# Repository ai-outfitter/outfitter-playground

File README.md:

# Playground

> [!IMPORTANT]
> This review branch is the PCB-workflow playground. It temporarily pins the
> stacked community-profiles work in PRs
> [#88](https://github.com/ai-outfitter/community-profiles/pull/88),
> [#90](https://github.com/ai-outfitter/community-profiles/pull/90), and
> [#96](https://github.com/ai-outfitter/community-profiles/pull/96), and
> [#102](https://github.com/ai-outfitter/community-profiles/pull/102), selects
> `hardware-engineer`, and enables `pcb-design`. The profile is exercised
> against `hardware/pnb-1`: an ESP32-S3 board whose shared I2C bus carries an
> SCD41 CO2 sensor and BH1750 light sensor. Run `npm run pcb:build` to rebuild
> the routed board and its JLCPCB-compatible fabrication package.
>
> `npm run test:pcb-workflow` still checks the workflow's consumer resolution
> independently. `npm run pcb:build` proves the design toolchain, including a
> live KiCad MCP inventory/project/schematic-ERC/board validation, typed ERC
> with injected failures, numerical margins, pcbnew construction, a validated
> routed seed (with explicit bounded freerouting regeneration), all-severity DRC, and
> Gerber/BOM/CPL generation. Its supplier gate must match every fitted part and
> record PCB, component, assembly, shipping, tariff/duty, tax, and other fees
> as one reconciled landed-cost quote. It never submits an order and cannot
> establish physical acceptance. Replace the branch pin with the release
> containing the stack before this work is eligible for `main`.

One pass through this repository teaches you how to use
[Outfitter](https://github.com/ai-outfitter/outfitter): you end with your
own copy of this repo whose committed [`.agents/`](.agents/settings.yml)
directory gave you a full agent roster from one pinned
[community catalog](https://github.com/ai-outfitter/community-profiles) — no
per-laptop setup — and you will have watched that roster run a real software
development lifecycle against a seeded bug: a scoped issue, an implementation
on a semantic branch, a CI-gated draft pull request, a cold-context
adversarial review, and a pull request left ready for you — the human — to
merge. Then you reset your copy and run it again, with a different harness,
prompt, or division of labor.

1. **Generate your playground** — a copy from this template, not a fork:
   forks need one-time UI clicks before Actions run and issues work;
   generated repos have both from the first commit (needs
   [Node.js](https://nodejs.org) 22.19+, [`gh`](https://cli.github.com/), and
   [`github-mcp-server`](https://github.com/github/github-mcp-server/releases/latest)
   on `PATH`; on macOS, install the server with
   `brew install github-mcp-server`):

   ```sh
   gh repo create outfitter-playground --template ai-outfitter/outfitter-playground --public --clone
   cd outfitter-playground
   git remote add upstream https://github.com/ai-outfitter/outfitter-playground.git
   ```

2. **Meet the bug:**

   ```sh
   node bin/split.js 100 3   # totals $99.99 — there's the seeded bug
   npm test                  # green: the suite misses the case
   ```

3. **Start Outfitter** — sync the pinned catalog, then launch. Pass
   `--harness claude` or `--harness codex` to run the same composed profile
   in a different harness, and on your first run in a harness type `/login`
   at its prompt to set up a model provider before pasting anything:

   ```sh
   npm install -g @ai-outfitter/outfitter
   outfitter sync
   export GITHUB_PERSONAL_ACCESS_TOKEN="$(gh auth token)"   # the agents' github MCP reads this
   outfitter run engineer   # the review branch defaults to hardware-engineer
   ```

4. **Paste this bug report** — nothing more; the process comes from the
   agent's loadout, not the prompt:

   ```text
   Splitting $100 among 3 people loses a cent — `node bin/split.js 100 3`
   totals $99.99. The shares should always sum to the amount. Do not merge.
   ```

5. **Watch the SDLC happen.** The engineer's loadout carries the lifecycle:
   its
   [`scoped-issues` skill](https://github.com/ai-outfitter/community-profiles/blob/main/skills/scoped-issues/SKILL.md)
   reproduces the report and files the scoped issue itself (acceptance
   criteria a reviewer can check mechanically), then it fixes `src/split.js`
   on a `fix/...` branch with a conventional commit, adds the regression
   test the issue demands, verifies with `npm test`, opens the pull request
   as a draft, waits for CI to go green, and marks it ready — then, per its
   `code-review` skill, **reviews its own PR adversarially**: it spawns
   cold-context subagents that judge only the diff, the criteria, and the
   checks, aggregates their JSON findings, posts one formal review through
   the github MCP, and fixes what blocks.
6. **Read the adversarial review.** The judgment comes from subagents with
   no stake in the change passing. Expect a formal PR review: one inline
   comment per finding, `REQUEST_CHANGES` if anything blocks, a `COMMENT`
   verdict when clean — never `APPROVE`, because approval is yours. To run
   a review pass by hand (or re-review a revision), start the engineer
   again:

   ```sh
   outfitter run engineer
   ```

   ```text
   Review the open pull request against its linked issue's acceptance
   criteria.
   ```
7. **Merge the ready PR.** Verify the acceptance criteria yourself, then
   merge:

   ```sh
   node bin/split.js 100 3   # total must read $100.00
   npm test
   gh pr merge --squash
   ```

That loop — issue → implementation → adversarial review → human merge — is
the whole lesson. [docs/workflows/engineer.md](docs/workflows/engineer.md)
walks the same loop with more control at each step, including delegating the
issue-writing to `git-forge-delegator` and swapping yourself into either
lane.

## Reset and go again

Throw away the run and restore your copy to the upstream state:

```sh
git checkout main
git fetch upstream && git reset --hard upstream/main
git push --force origin main
git branch | grep -v ' main$' | xargs -r git branch -D   # local branches
gh pr list --state open --json number --jq '.[].number' \
  | xargs -rn1 gh pr close --delete-branch                # open PRs + branches
```

Closed issues and merged PRs stay in your copy's history — that is fine;
the next run starts from a fresh issue. (No `upstream` remote?
`git remote add upstream https://github.com/ai-outfitter/outfitter-playground.git`.)

## Take the workflow to a real project

The playground proves the loop; your `.agents/` tree is what makes the
method durable. Run `outfitter setup` from a real project to create project
or user configuration. To share the same agents and skills across a team,
create a personal or organization `.agents` repository in the
[Outfitter dashboard](https://ai-outfitter.com/dashboard/), then follow
[Share one catalog](https://ai-outfitter.com/docs/outfitter/runbooks/share-one-catalog/)
to pin, sync, and verify it.

## The exhibit

`split` is a zero-dependency Node CLI that splits a bill among people. Its
bug is deliberate: shares are floored, so uneven amounts lose cents while
the six-test suite stays green — fixing it requires both a code change and a
regression test, which gives the reviewer something real to check. The bug
report with acceptance criteria is seeded at
[docs/issues/0001-split-loses-cents.md](docs/issues/0001-split-loses-cents.md).

> [!NOTE]
> The bug stays unfixed **upstream on purpose** — it is the exhibit. Fix it
> in your generated copy as often as you like; pull requests fixing it here
> will be declined with thanks.

## Layout

```text
.agents/settings.yml     Outfitter settings: pinned community-profiles source
docs/issues/             seeded bug reports to file with `gh issue create`
docs/workflows/          workflow walkthroughs
src/split.js             the library (the bug lives here)
bin/split.js             the CLI
test/split.test.js       the suite that passes anyway
AGENTS.md                repository instructions agents follow (CLAUDE.md symlinks to it)
```

## Demo it

[e2e/demo.sh](e2e/README.md) launches the engineer session with everything
wired from what you already have — valid GitHub CLI authentication and your
Claude Code/Codex logins — under a persistent, isolated HOME in `/tmp`. It
runs in this checkout, whose origin must be **your generated playground** (the
script refuses an org-repo origin and verifies template lineage), and resets
it to the upstream state each run so issues and PRs land on your copy and the
seeded bug is back. Pick a harness per run; `check` is a free sanity pass that
does not require or inspect GitHub credentials (its catalog sync is the only
networked step), and `reset` wipes the demo HOME.

```sh
e2e/demo.sh            # claude — or: pi, codex, check, reset
```

## License

[MIT](LICENSE.md)

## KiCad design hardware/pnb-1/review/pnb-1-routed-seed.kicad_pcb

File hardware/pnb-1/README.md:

# PNB-1 environmental sensor node

PNB-1 is an ESP32-S3-MINI-1 board with USB-C, an SCD41 CO2/temperature/
humidity sensor at I2C address `0x62`, and a BH1750 light sensor at address
`0x23`. It is the real PCB fixture exercised by the playground's
`hardware-engineer` profile.

Requirements live in `docs/hardware/pnb-1.md`; the daughter connector is
defined by `docs/hardware/pod-node-contract.md`.

## Reproducible flow

SKiDL -> standard KiCad netlist -> pcbnew -> freerouting -> KiBot. The root
devenv provides KiCad, pcbnew, freerouting, EasyEDA import, and ngspice;
`hardware/.venv` provides the pinned Python tools. Set
`V=../.venv/bin/python` while working in this directory.

| Stage | Source or command | Evidence |
| --- | --- | --- |
| setup | `npm run pcb:setup` | pinned tool availability and versions |
| schematic | `$V pnb1_skidl.py && $V build.py` | typed ERC, independent vendor pad-map check, generated KiCad schematic, and all-severity KiCad ERC |
| fault test | `PNB_FAULT=short-3v3-to-sda $V pnb1_skidl.py` | required nonzero exit |
| margins | `$V verify_margins.py` | peak-current, thermal, and pull-up checks |
| build | `$V build.py` | footprints, placement, outline, and BOM |
| route | `$V route.py` | validated committed routed seed and zero-error/unconnected DRC |
| reroute | `PNB_ROUTE_REGENERATE=1 $V route.py` | bounded freerouting regeneration for layout iteration |
| release | `$V -m kibot -b pnb-1.kicad_pcb -c pnb-1.kibot.yaml -d fab` | Gerbers, drill files, CPL, ZIP, and DRC reports |
| package | `npm run pcb:verify-package` | BOM/CPL agreement and checksummed manifest |
| quote | authenticated supplier dry run; `npm run pcb:verify-quote` | all fitted parts plus reconciled fabrication, assembly, shipping, tariff/duty, tax, and other fees; no purchase |

`schematic.py` is the independent connectivity and numeric model; `verify.py`
cross-checks it against the vendor-derived library and generates
`sch/pnb-1.kicad_sch`. The committed DRC-clean routed seed makes normal builds
reproducible; an explicit regeneration reruns freerouting and replaces the seed
only after the corrected result passes DRC.
The fabrication package feeds an authenticated supplier dry run. A complete
quote proves only point-in-time supplier matching, availability, and landed
cost; it does not authorize an order or claim physical acceptance. J3 is
deliberately DNP in the assembly package and remains as a hand-installable
daughter-header footprint.

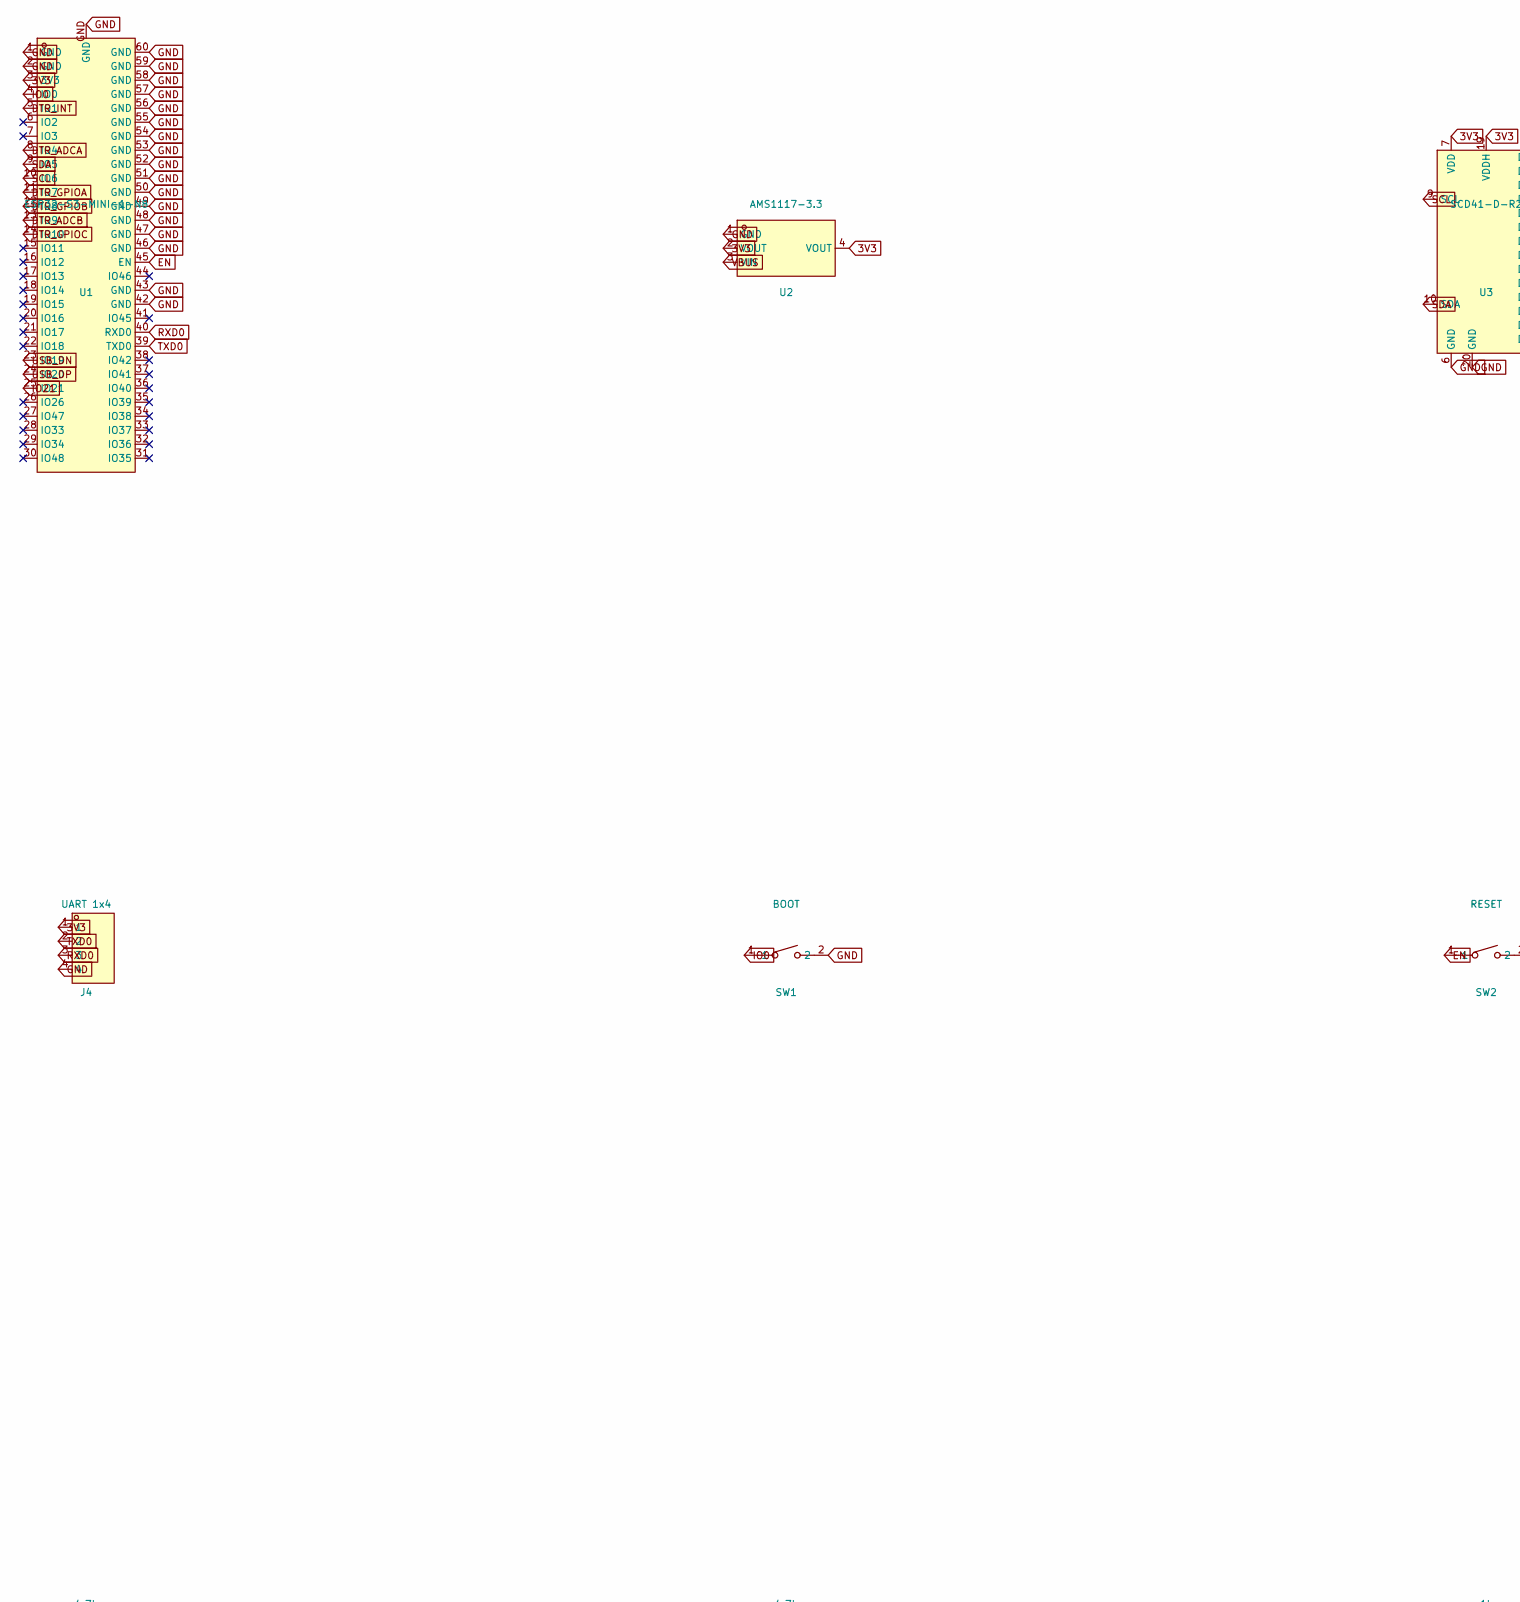
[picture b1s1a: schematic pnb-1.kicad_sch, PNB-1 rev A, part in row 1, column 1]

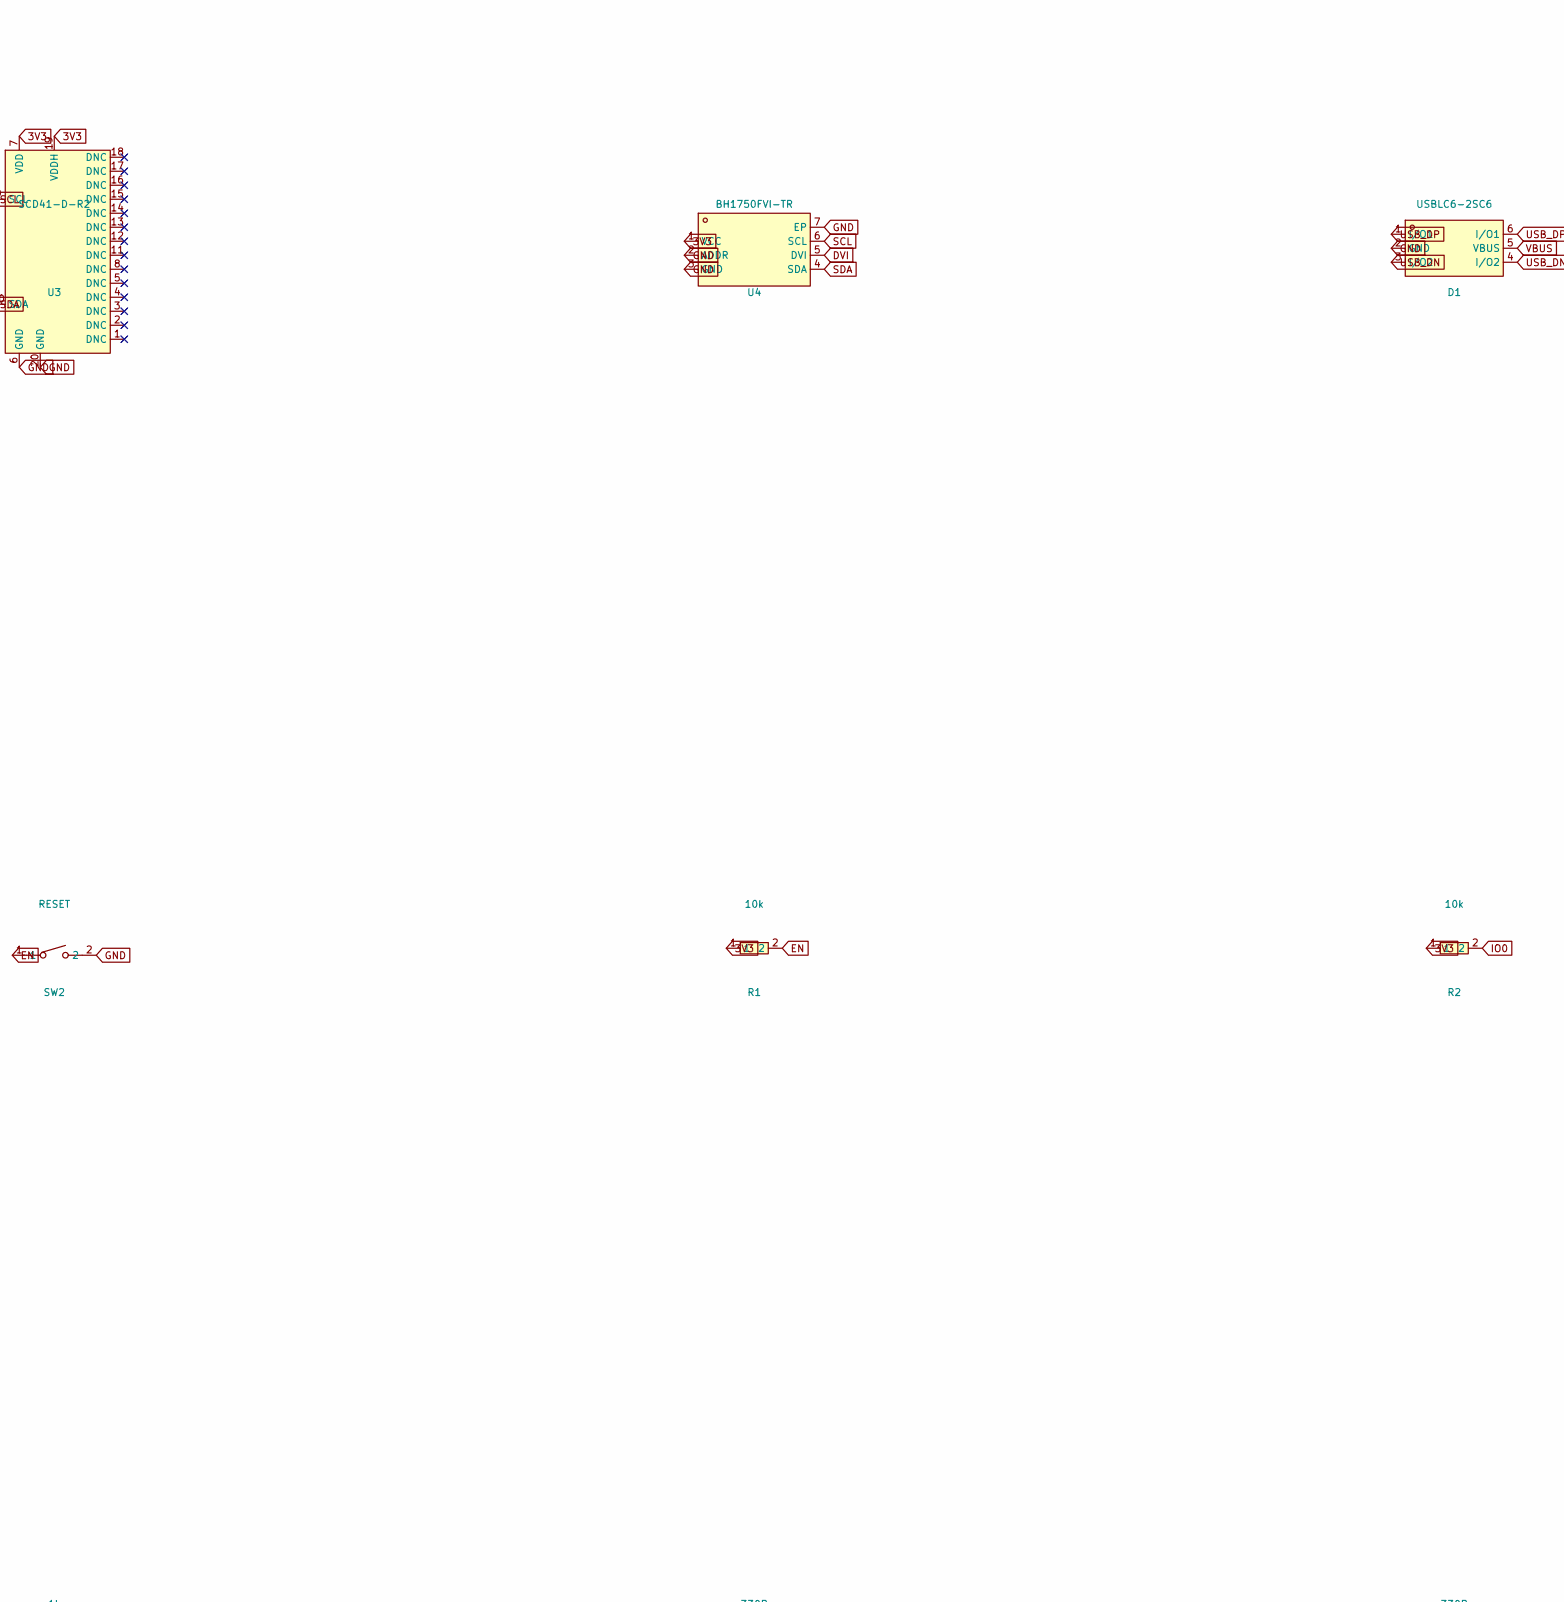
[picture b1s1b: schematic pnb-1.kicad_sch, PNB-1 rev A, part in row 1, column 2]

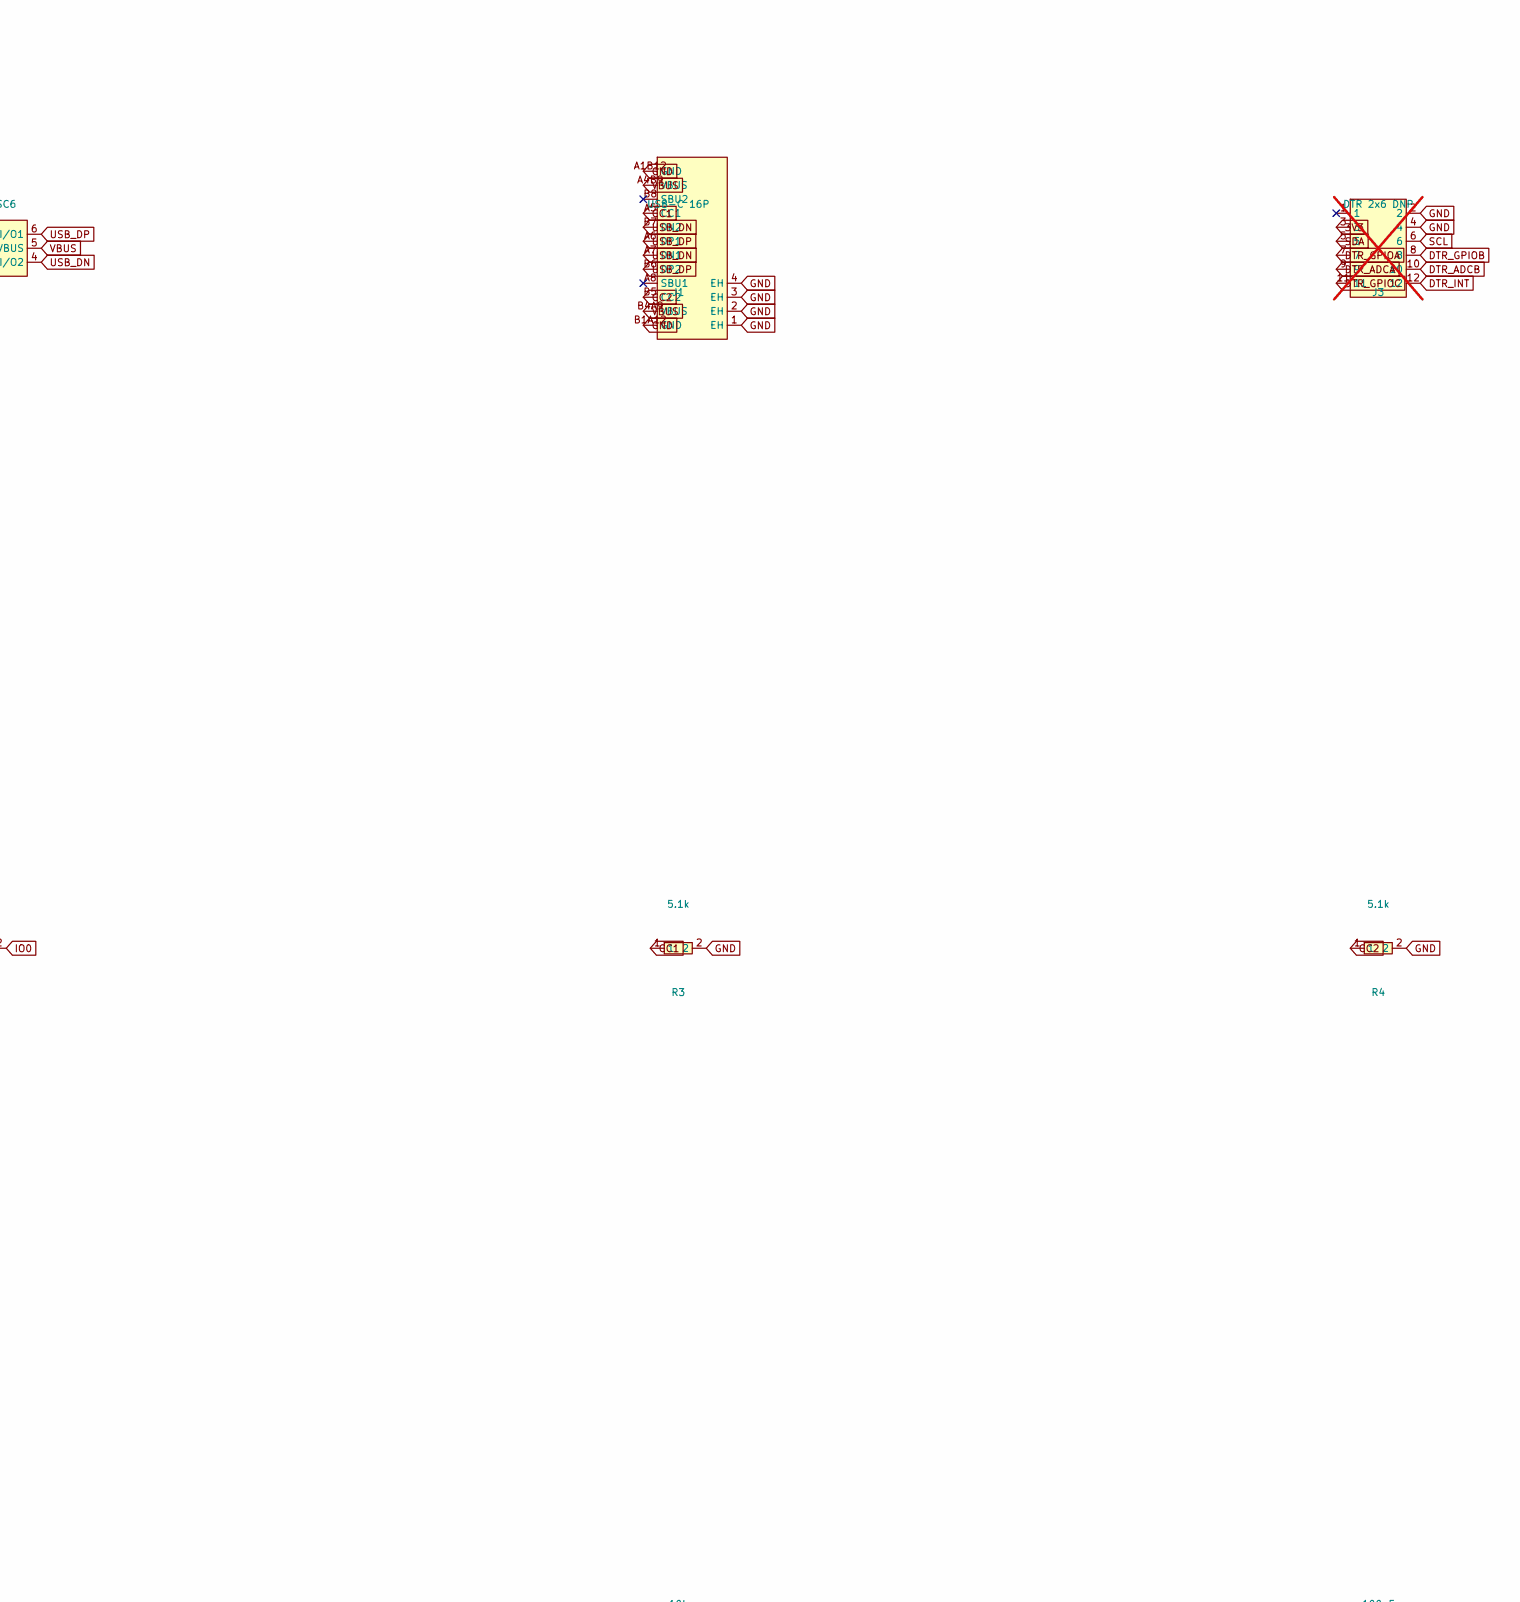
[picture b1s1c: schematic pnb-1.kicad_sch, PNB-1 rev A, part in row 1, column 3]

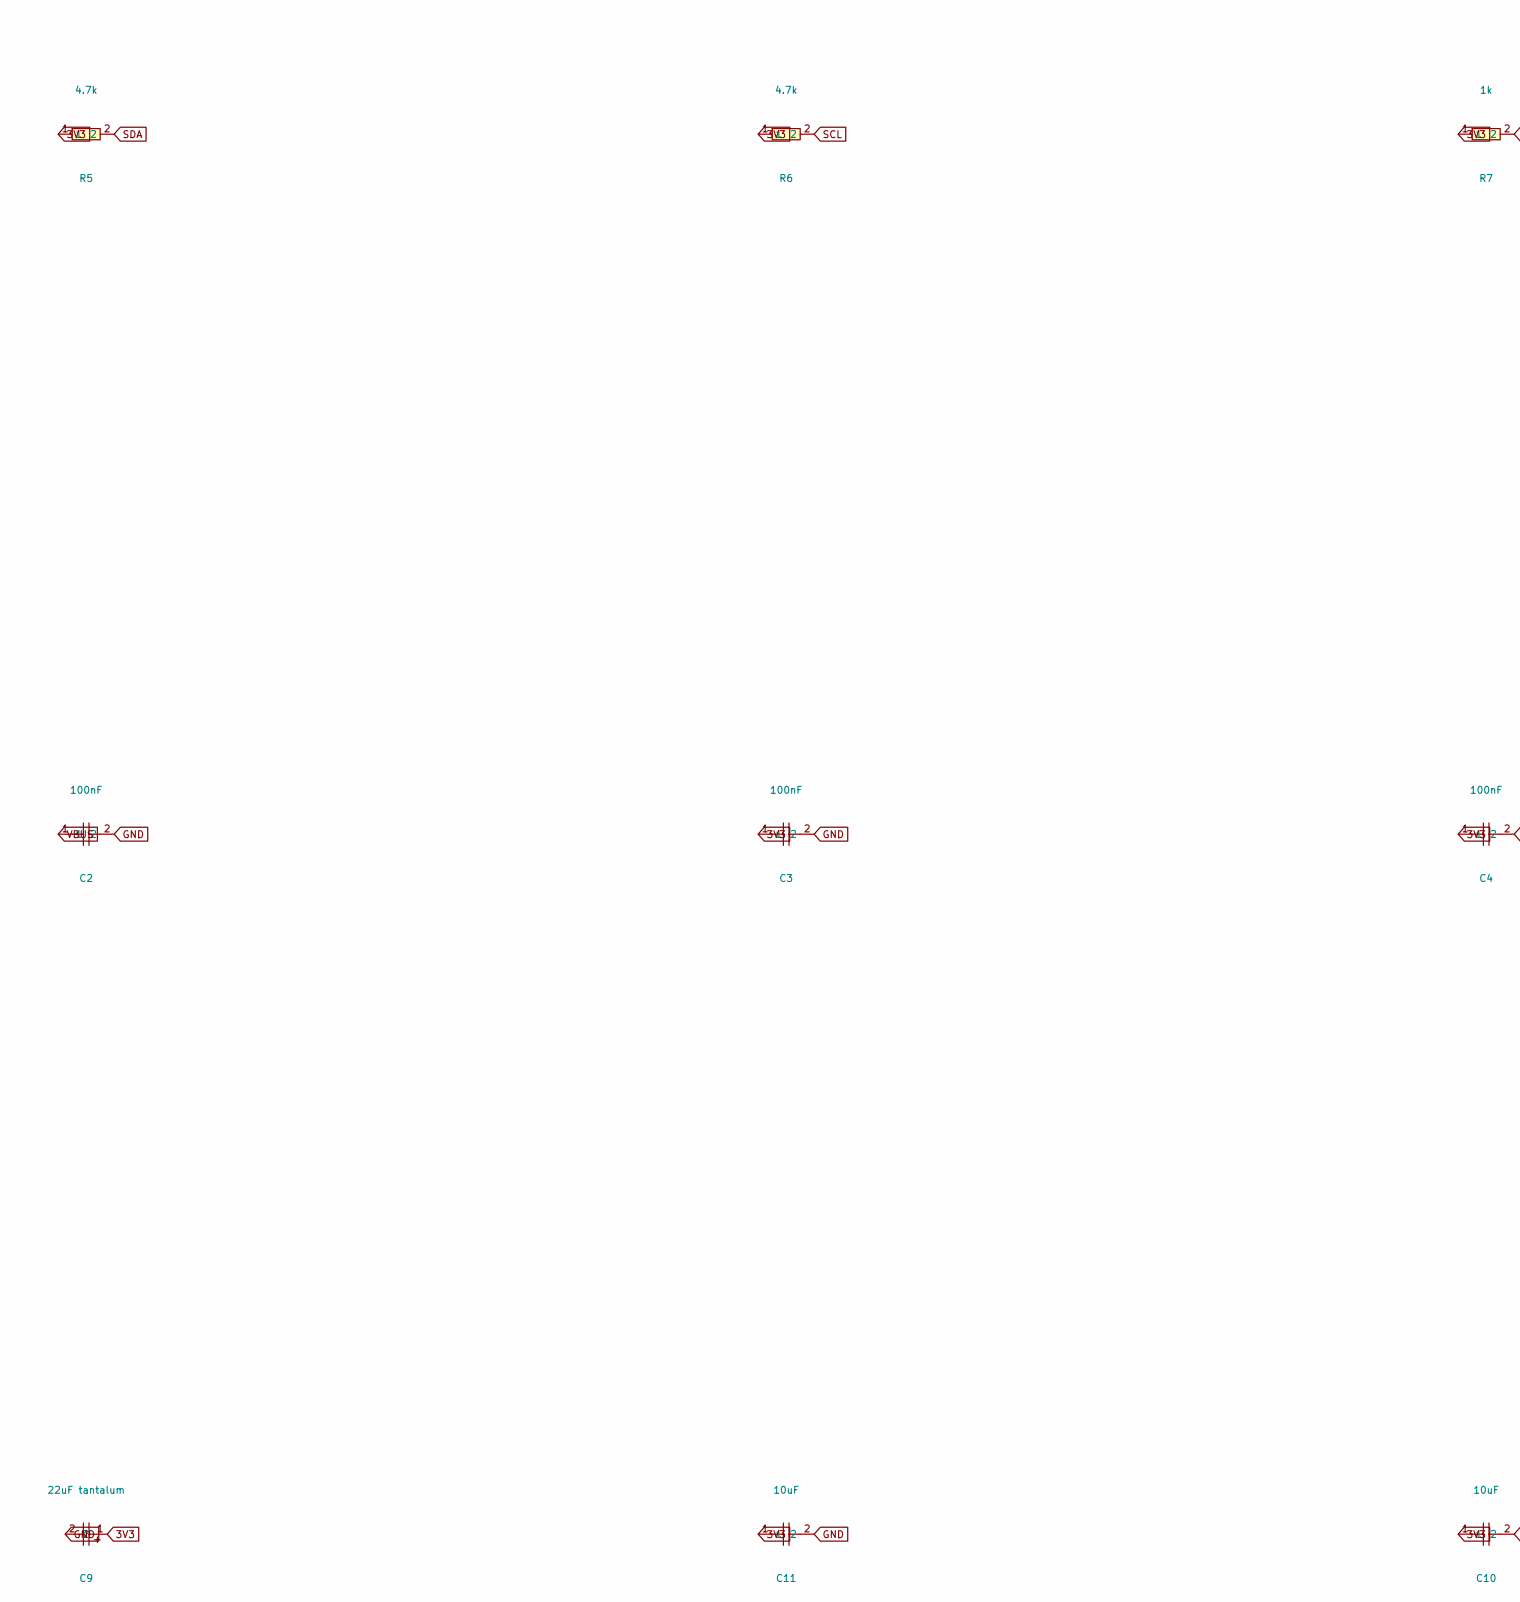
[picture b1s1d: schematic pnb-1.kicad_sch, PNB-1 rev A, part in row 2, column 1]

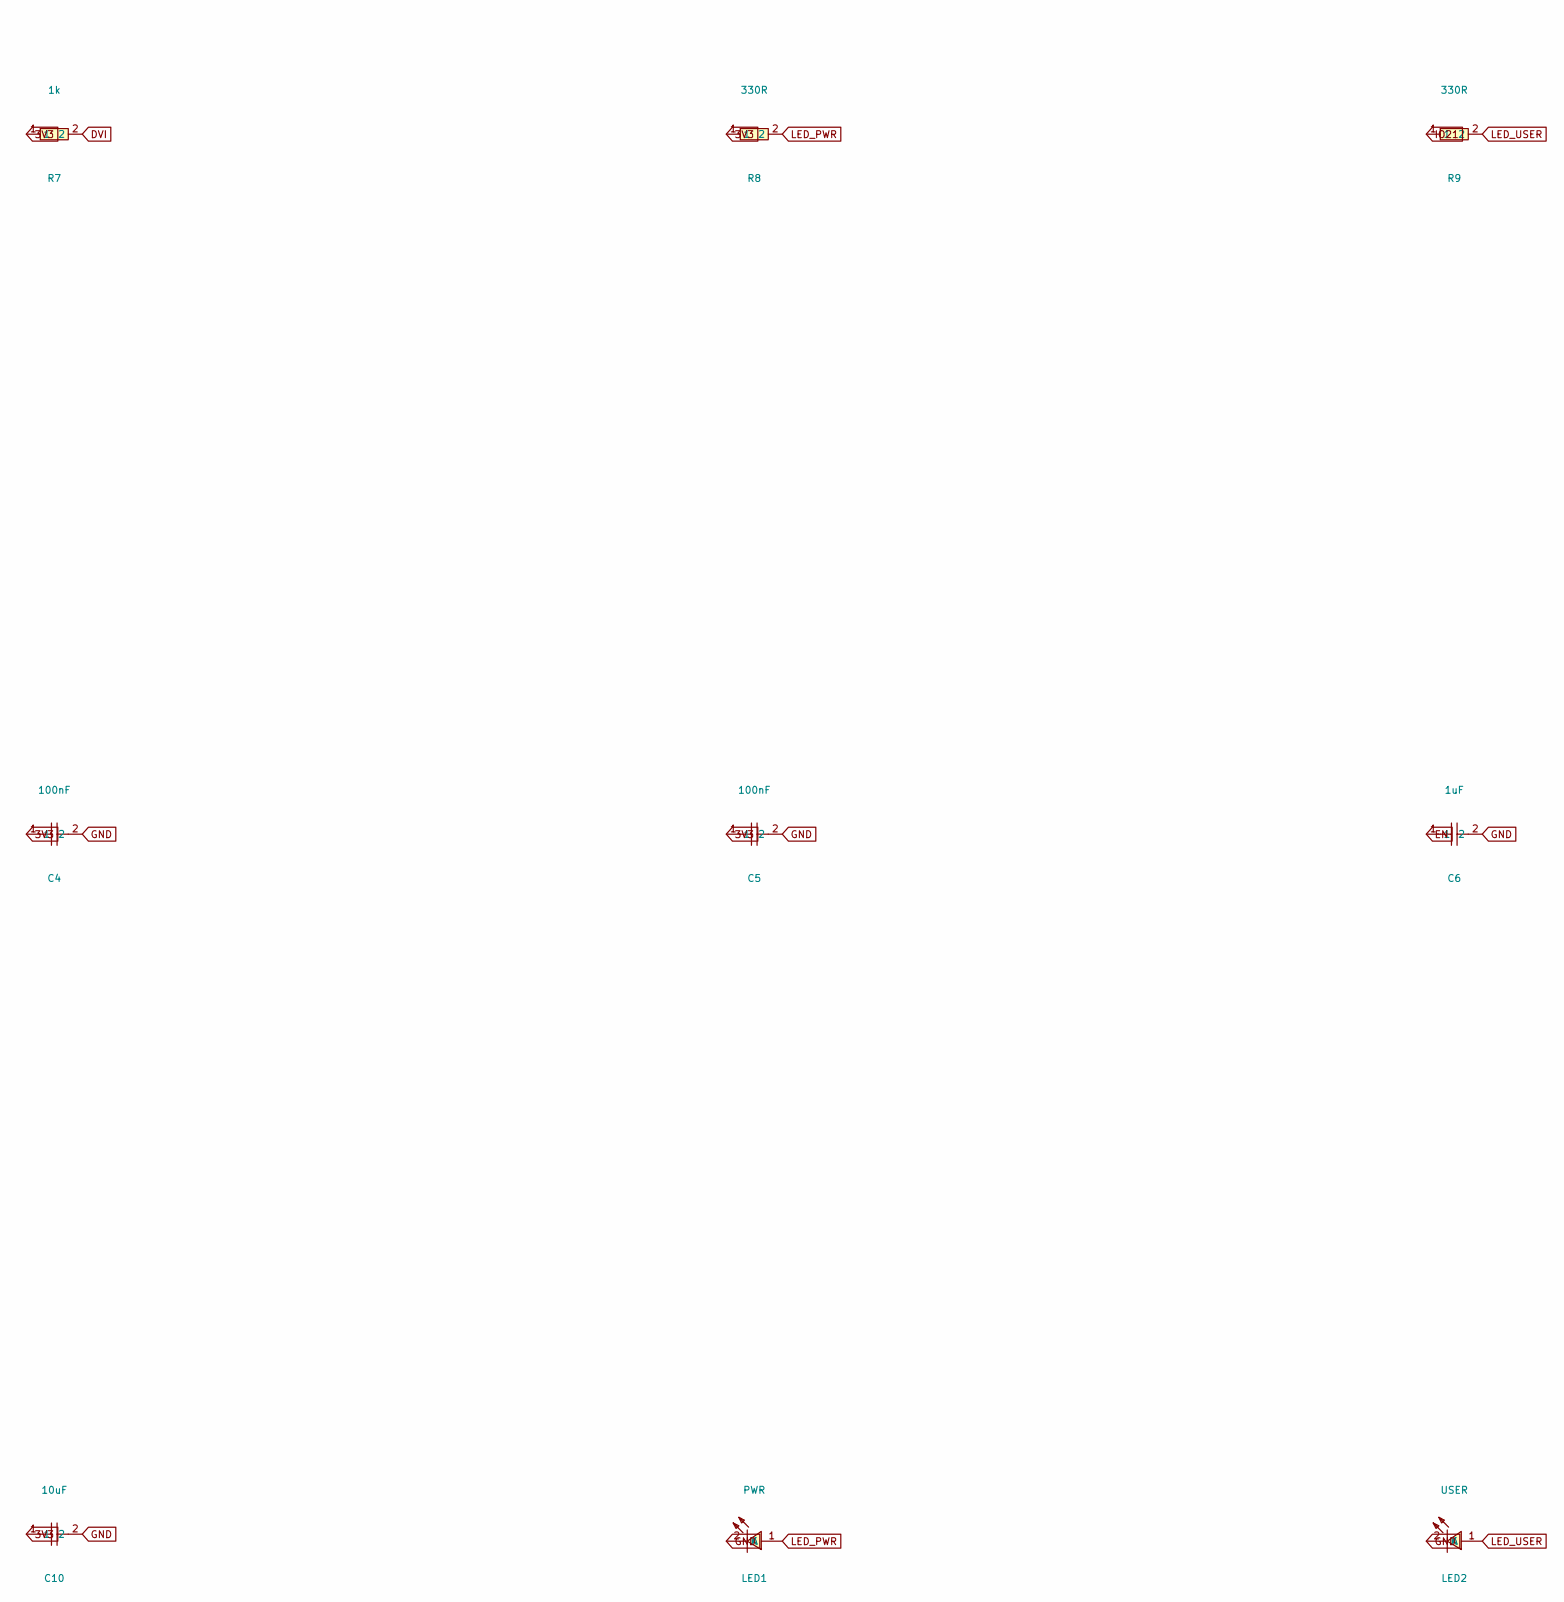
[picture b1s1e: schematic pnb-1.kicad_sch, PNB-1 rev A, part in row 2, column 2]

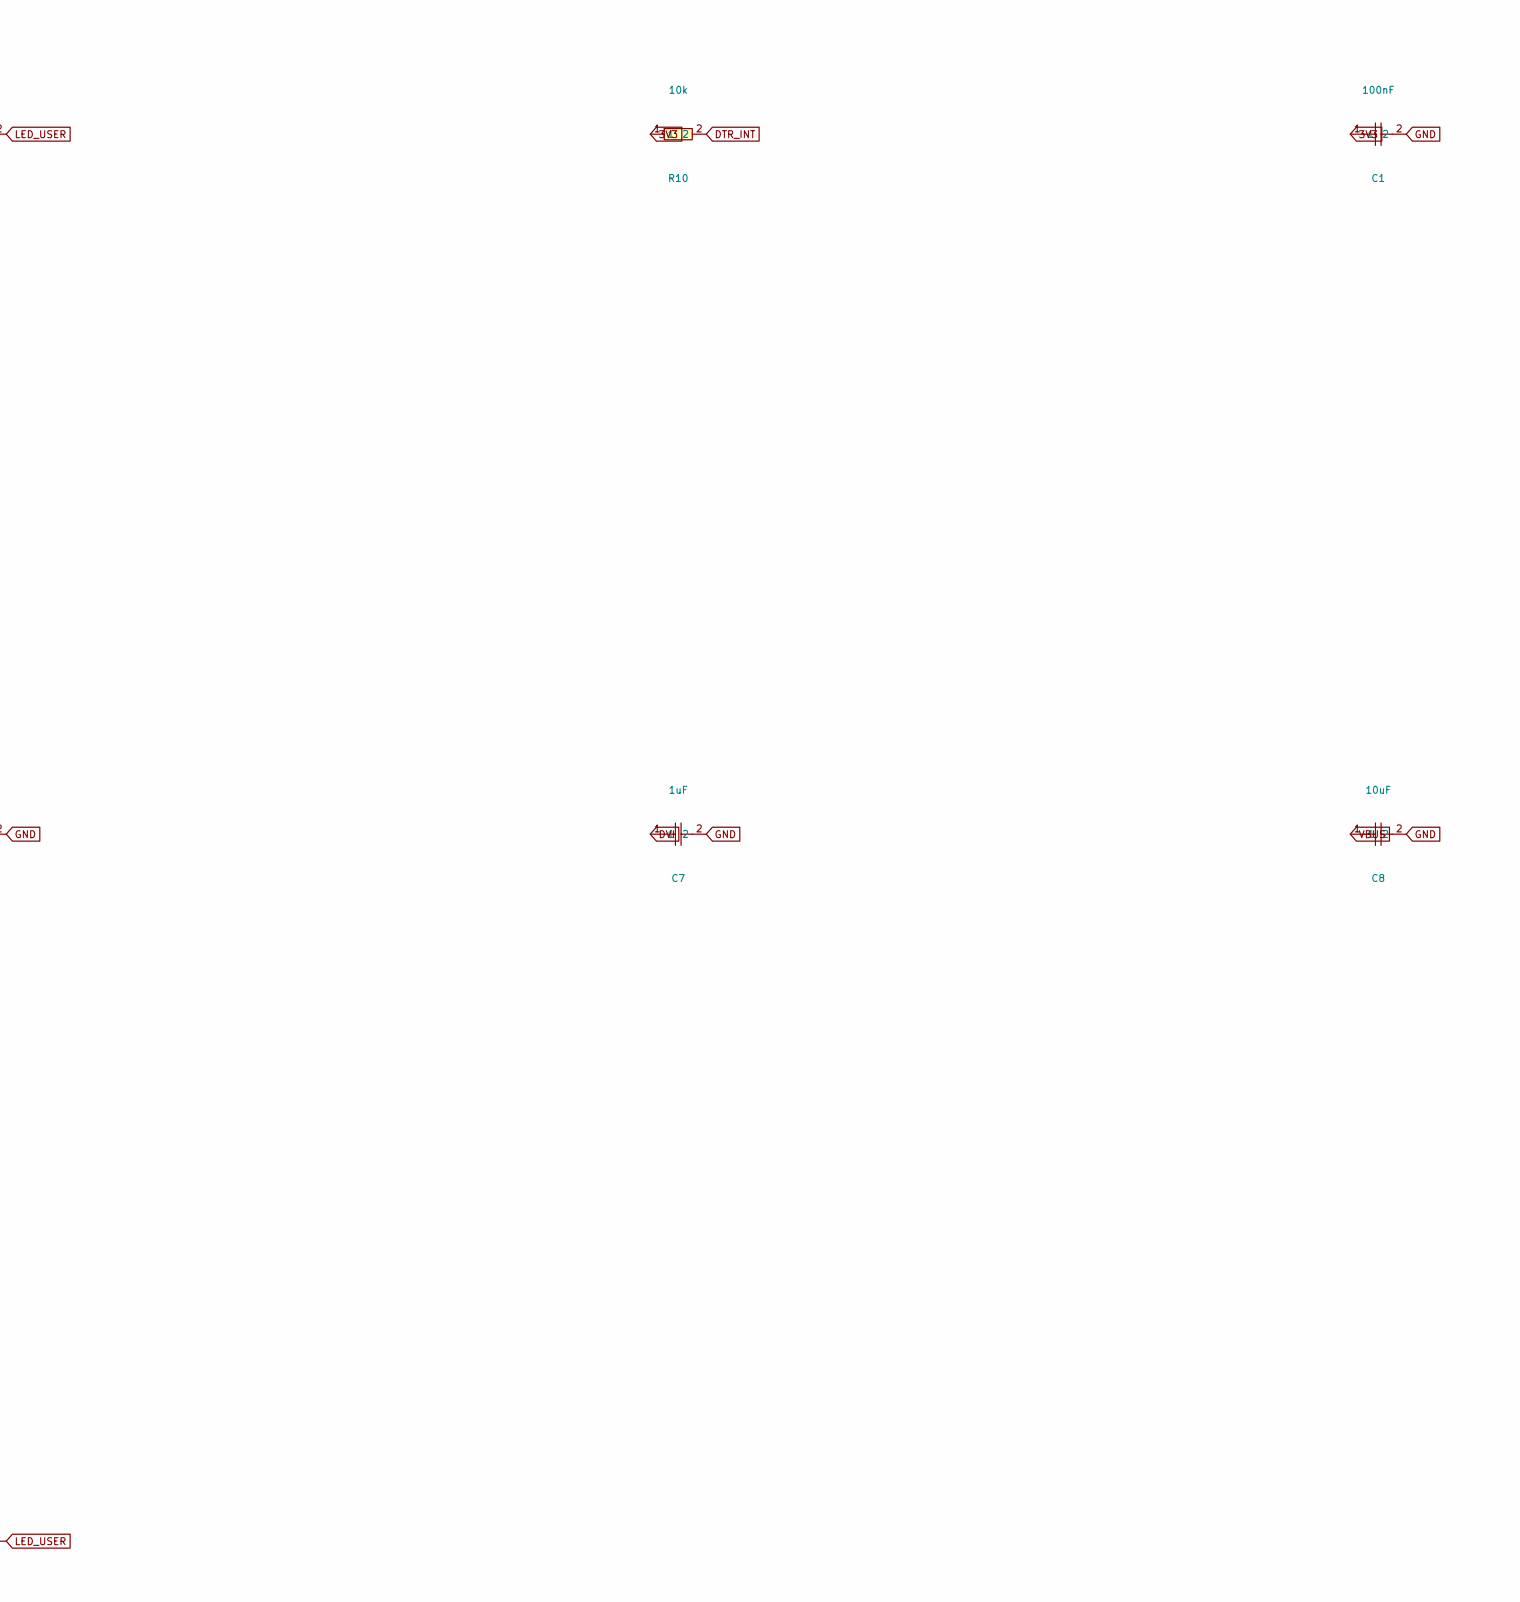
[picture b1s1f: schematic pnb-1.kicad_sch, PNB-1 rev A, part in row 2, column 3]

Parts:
C1, C2, C3, C4, C5: 100nF; C0603
C6, C7: 1uF; C0603
C8, C10, C11: 10uF; C0805
C9: 22uF tantalum; CASE-A_3216
D1: USBLC6-2SC6; SOT-23-6_L2.9-W1.6-P0.95-LS2.8-BL
J1: USB-C 16P; USB-C_SMD-TYPE-C-31-M-12_1
J3: DTR 2x6 DNP; HDR-TH_12P-P2.54-V-M-R2-C6-S2.54; not fitted
J4: UART 1x4; HDR-TH_4P-P2.54-V-M
LED1: PWR; LED-SMD_L1.6-W0.8-R-RD
LED2: USER; LED-SMD_L1.6-W0.8-R-RD
R1, R2, R10: 10k; R0603
R3, R4: 5.1k; R0603
R5, R6: 4.7k; R0603
R7: 1k; R0603
R8, R9: 330R; R0603
SW1: BOOT; SW-SMD_L3.9-W3.0-P4.45
SW2: RESET; SW-SMD_L3.9-W3.0-P4.45
U1: ESP32-S3-MINI-1-N8; BULETM-SMD_ESP32-S3-MINI-1-N8
U2: AMS1117-3.3; SOT-223-3_L6.5-W3.4-P2.30-LS7.0-BR
U3: SCD41-D-R2; LGA-20_L10.1-W10.1-P1.25-TL_SCD41-D-R2
U4: BH1750FVI-TR; WSOF-6_L2.6-W1.6-P0.50-TL-EP

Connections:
3V3: C1.1, C3.1, C4.1, C5.1, C9.1, C10.1, C11.1, J3.3, J4.1, R1.1, R2.1, R5.1, R6.1, R7.1, R8.1, R10.1, U1.3 (3V3), U2.2 (VOUT), U2.4 (VOUT), U3.7 (VDD), U3.19 (VDDH), U4.1 (VCC)
CC1: J1.A5 (CC1), R3.1
CC2: J1.B5 (CC2), R4.1
DTR_ADCA: J3.9, U1.8 (IO4)
DTR_ADCB: J3.10, U1.13 (IO9)
DTR_GPIOA: J3.7, U1.11 (IO7)
DTR_GPIOB: J3.8, U1.12 (IO8)
DTR_GPIOC: J3.11, U1.14 (IO10)
DTR_INT: J3.12, R10.2, U1.5 (IO1)
DVI: C7.1, R7.2, U4.5 (DVI)
EN: C6.1, R1.2, SW2.1, U1.45 (EN)
GND: C1.2, C2.2, C3.2, C4.2, C5.2, C6.2, C7.2, C8.2, C9.2, C10.2, C11.2, D1.2 (GND), J1.1 (EH), J1.2 (EH), J1.3 (EH), J1.4 (EH), J1.A1B12 (GND), J1.B1A12 (GND), J3.2, J3.4, J4.4, LED1.2 (K), LED2.2 (K), R3.2, R4.2, SW1.2, SW2.2, U1.1 (GND), U1.2 (GND), U1.42 (GND), U1.43 (GND), U1.46 (GND), U1.47 (GND), U1.48 (GND), U1.49 (GND), U1.50 (GND), U1.51 (GND), U1.52 (GND), U1.53 (GND), U1.54 (GND), U1.55 (GND), U1.56 (GND), U1.57 (GND), U1.58 (GND), U1.59 (GND), U1.60 (GND), U1.GND, U2.1 (GND), U3.6 (GND), U3.20 (GND), U4.2 (ADDR), U4.3 (GND), U4.7 (EP)
IO0: R2.2, SW1.1, U1.4 (IO0)
IO21: R9.1, U1.25 (IO21)
LED_PWR: LED1.1 (A), R8.2
LED_USER: LED2.1 (A), R9.2
RXD0: J4.3, U1.40 (RXD0)
SCL: J3.6, R6.2, U1.10 (IO6), U3.9 (SCL), U4.6 (SCL)
SDA: J3.5, R5.2, U1.9 (IO5), U3.10 (SDA), U4.4 (SDA)
TXD0: J4.2, U1.39 (TXD0)
USB_DN: D1.3 (I/O2), D1.4 (I/O2), J1.A7 (DN1), J1.B7 (DN2), U1.23 (IO19)
USB_DP: D1.1 (I/O1), D1.6 (I/O1), J1.A6 (DP1), J1.B6 (DP2), U1.24 (IO20)
VBUS: C2.1, C8.1, D1.5 (VBUS), J1.A4B9 (VBUS), J1.B4A9 (VBUS), U2.3 (VIN)

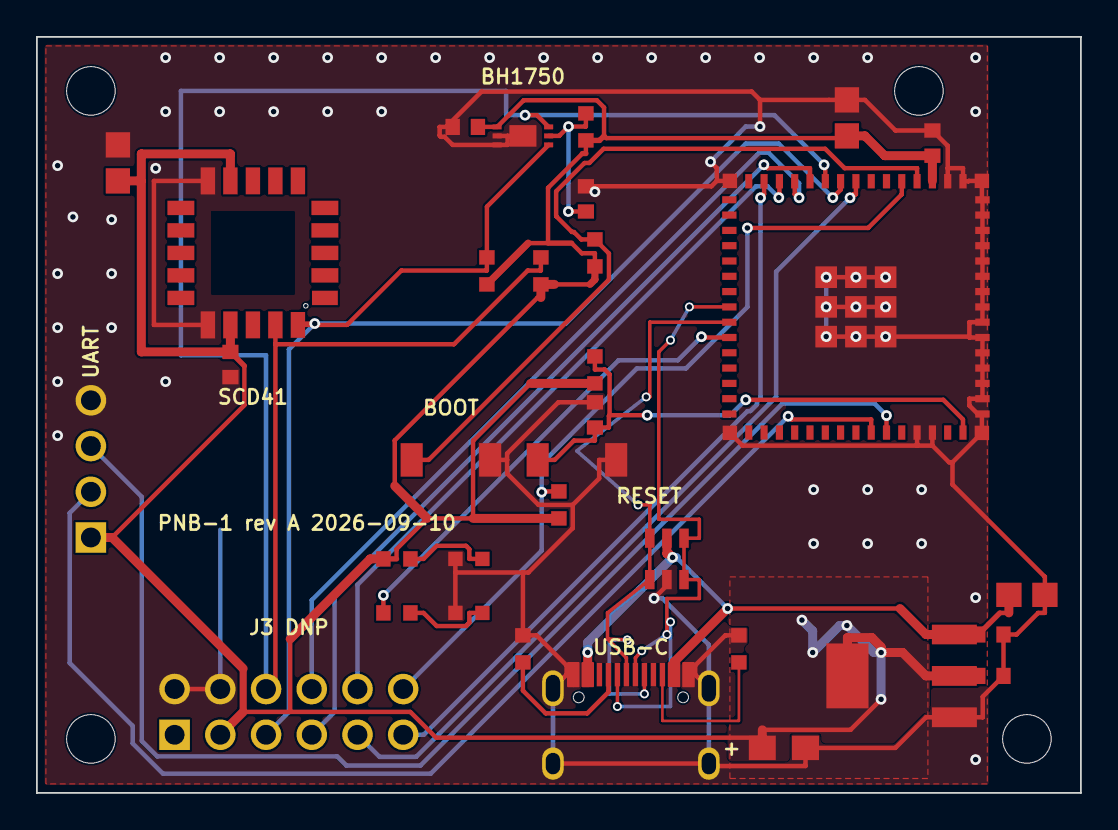
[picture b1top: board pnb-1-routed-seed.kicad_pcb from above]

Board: 2 copper layers, 58.0 x 42.0 mm, 37 parts (0 on the bottom side), 23 nets.

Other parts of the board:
H1, H2, H3, H4: M2.5

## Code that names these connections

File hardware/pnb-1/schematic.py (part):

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    "LED_USER": [("R9", "2"), ("LED2", "1")],
    "TXD0": [("U1", "39"), ("J4", "2")],
    "RXD0": [("U1", "40"), ("J4", "3")],
    "DTR_GPIOA": [("U1", "11"), ("J3", "7")],   # IO7
    "DTR_GPIOB": [("U1", "12"), ("J3", "8")],   # IO8
    "DTR_ADCA": [("U1", "8"), ("J3", "9")],     # IO4
    "DTR_ADCB": [("U1", "13"), ("J3", "10")],   # IO9
    "DTR_GPIOC": [("U1", "14"), ("J3", "11")],  # IO10
    "DTR_INT": [("U1", "5"), ("J3", "12"), ("R10", "2")],  # IO1, pulled up on the base
}

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    "SDA": {"U1": r"IO5", "U3": r"SDA", "U4": r"SDA"}, "SCL": {"U1": r"IO6", "U3": r"SCL", "U4": r"SCL"},
    "EN": {"U1": r"^EN"}, "IO0": {"U1": r"IO0$"}, "TXD0": {"U1": r"TXD0|IO43"}, "RXD0": {"U1": r"RXD0|IO44"},
    "IO21": {"U1": r"IO21"}, "DVI": {"U4": r"DVI"}, "CC1": {"J1": r"CC1"}, "CC2": {"J1": r"CC2"},
    "DTR_GPIOA": {"U1": r"IO7$"}, "DTR_GPIOB": {"U1": r"IO8$"}, "DTR_ADCA": {"U1": r"IO4$"},
    "DTR_ADCB": {"U1": r"IO9$"}, "DTR_GPIOC": {"U1": r"IO10$"}, "DTR_INT": {"U1": r"IO1$"},
}

# Numeric margins — the tier ERC cannot see. Values from datasheets / requirements.
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
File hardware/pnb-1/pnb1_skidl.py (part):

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    "U3": {"VDD": Pin.types.PWRIN, "VDDH": Pin.types.PWRIN, "GND": Pin.types.PWRIN,
           "SCL": Pin.types.INPUT, "SDA": Pin.types.BIDIR},
    "U4": {"VCC": Pin.types.PWRIN, "GND": Pin.types.PWRIN, "ADDR": Pin.types.INPUT,
           "SDA": Pin.types.BIDIR, "SCL": Pin.types.INPUT, "DVI": Pin.types.INPUT,
           "EP": Pin.types.PWRIN},
    "D1": {"GND": Pin.types.PWRIN, "VBUS": Pin.types.PWRIN},
    "J1": {"VBUS": Pin.types.PWROUT, "GND": Pin.types.PWROUT,  # upstream side sources power
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    R[_r][2].func = Pin.types.PULLUP
for _r in ("R3", "R4"):                            # CC Rd pull-downs
    R[_r][1].func = Pin.types.PULLDN
R["R8"][2].func = Pin.types.PULLUP                 # LED_PWR: tied to 3V3 via R8

# ---------------------------------------------------------------- nets
# Every connection below is by symbol pin NAME (passives/headers/switches have
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n_txd0 = Net("TXD0"); n_txd0 += u1["TXD0"], j4[2]
n_rxd0 = Net("RXD0"); n_rxd0 += u1["RXD0"], j4[3]

n_dtr_gpioa = Net("DTR_GPIOA"); n_dtr_gpioa += u1["IO7"], j3[7]
n_dtr_gpiob = Net("DTR_GPIOB"); n_dtr_gpiob += u1["IO8"], j3[8]
n_dtr_adca = Net("DTR_ADCA"); n_dtr_adca += u1["IO4"], j3[9]
n_dtr_adcb = Net("DTR_ADCB"); n_dtr_adcb += u1["IO9"], j3[10]
n_dtr_gpioc = Net("DTR_GPIOC"); n_dtr_gpioc += u1["IO10"], j3[11]
n_dtr_int = Net("DTR_INT"); n_dtr_int += u1["IO1"], j3[12], R["R10"][2]

# The acceptance harness sets this only for an expected-failure run. Joining a
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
